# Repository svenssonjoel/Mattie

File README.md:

# Mattie
stM32f4 lATTIcE - MATTIE - A PCB with an STM32f4 and a LATTICE FPGA

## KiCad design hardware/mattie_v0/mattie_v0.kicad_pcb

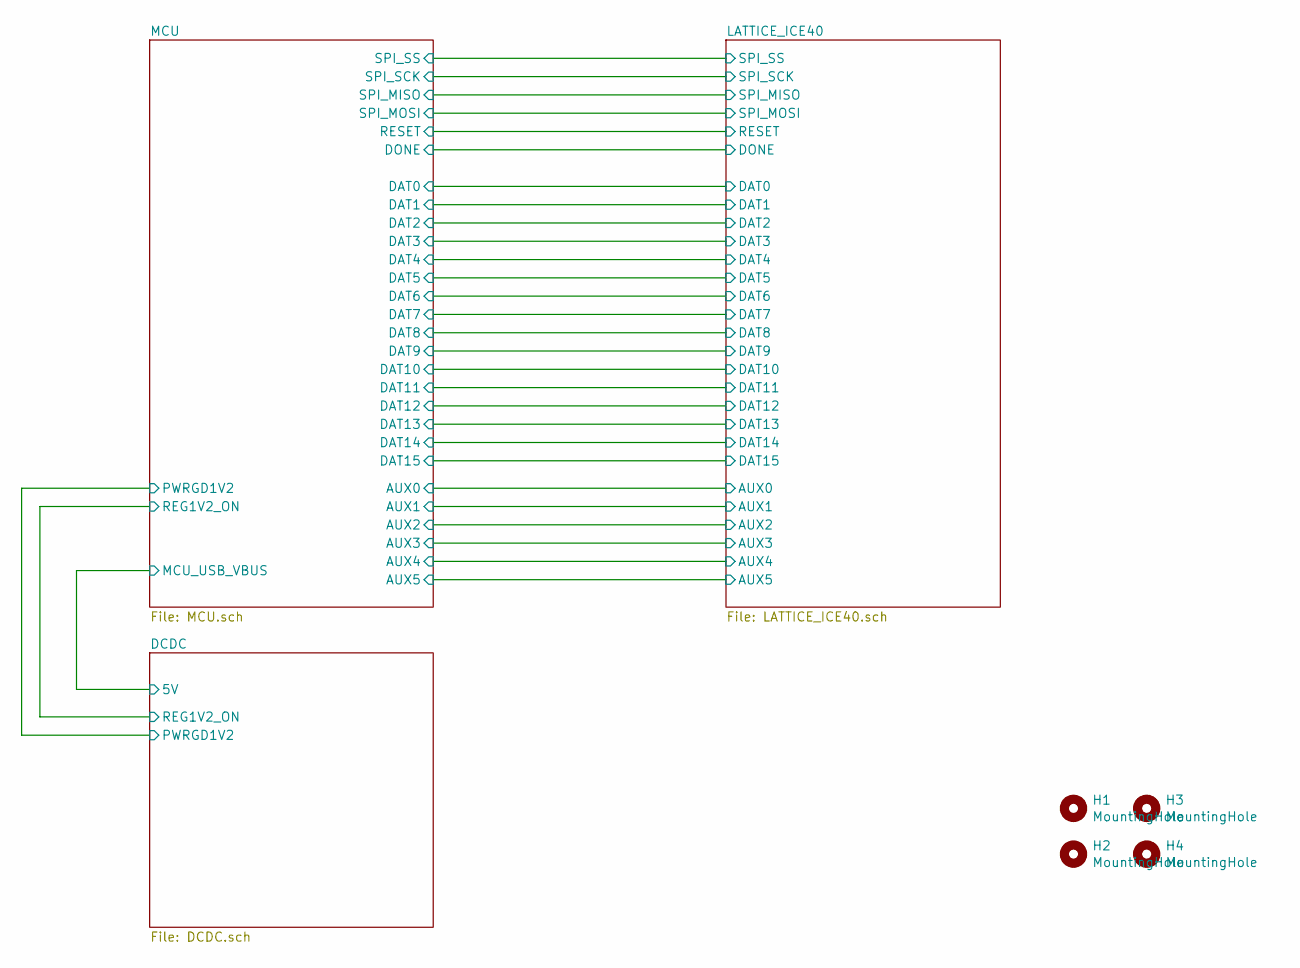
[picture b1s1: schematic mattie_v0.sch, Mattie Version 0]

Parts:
H1, H2, H3, H4: MountingHole; MountingHole_3.2mm_M3

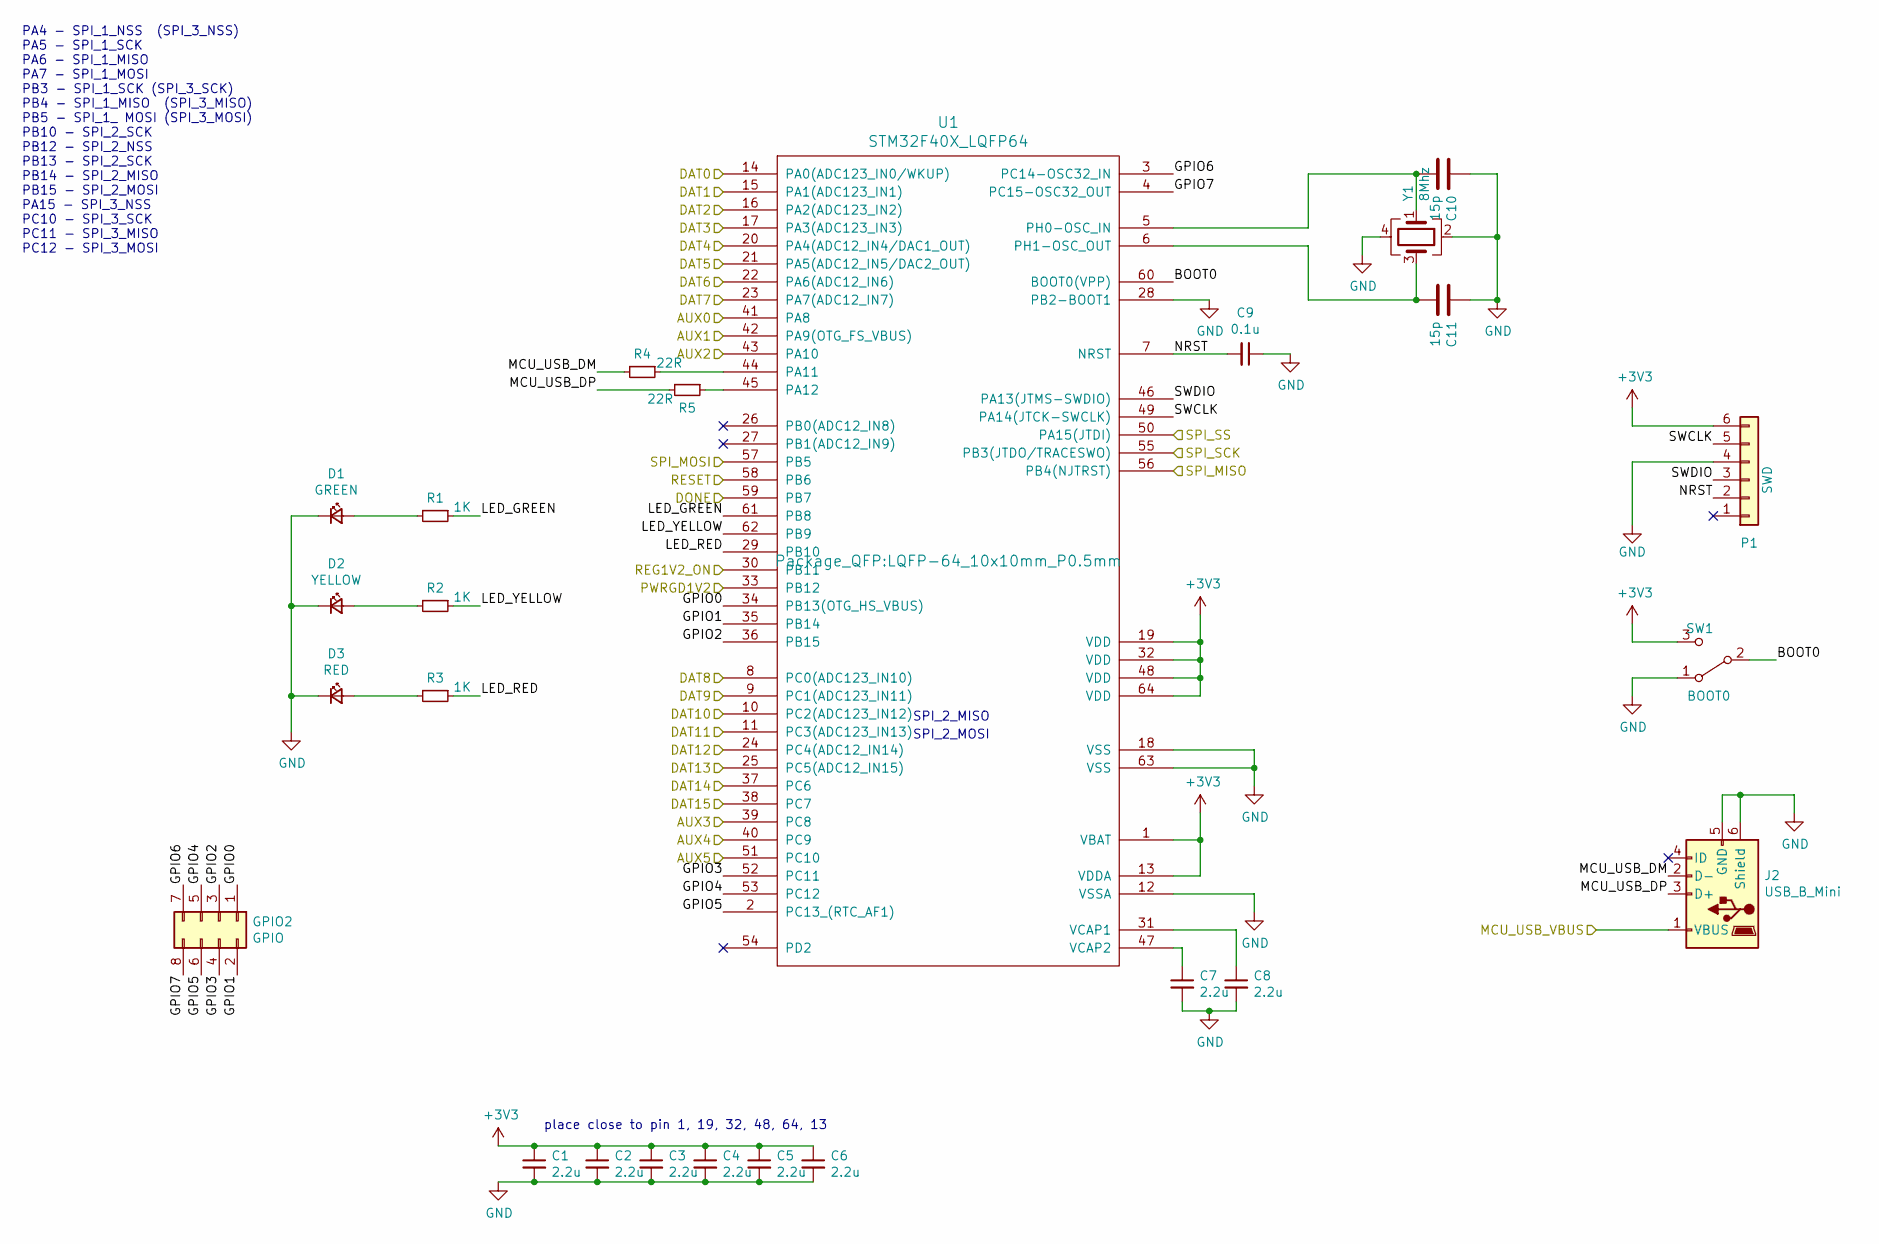
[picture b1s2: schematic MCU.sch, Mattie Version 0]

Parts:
C1, C2, C3, C4, C5, C6, C7, C8: 2.2u; C_0603_1608Metric
C9: 0.1u; C_0603_1608Metric
C10, C11: 15p; C_0603_1608Metric
D1: GREEN; LED_0603_1608Metric
D2: YELLOW; LED_0603_1608Metric
D3: RED; LED_0603_1608Metric
GPIO2: GPIO; PinHeader_2x04_P2.54mm_Vertical
J2: USB_B_Mini; USB_Mini-B_Lumberg_2486_01_Horizontal
P1: SWD; JST_PH_B6B-PH-K_1x06_P2.00mm_Vertical
R1, R2, R3: 1K; R_0603_1608Metric
R4, R5: 22R; R_0603_1608Metric
SW1: BOOT0; SW_SPDT_PCM12
U1: STM32F40X_LQFP64; LQFP-64_10x10mm_P0.5mm
Y1: 8Mhz; Crystal_SMD_5032-4Pin_5.0x3.2mm

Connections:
+3V3: C1.1, C2.1, C3.1, C4.1, C5.1, C6.1, P1.6, SW1.3 (C), U1.1 (VBAT), U1.13 (VDDA), U1.19 (VDD), U1.32 (VDD), U1.48 (VDD), U1.64 (VDD); also elsewhere on the board
/DCDC/5V: J2.1 (VBUS); also elsewhere on the board
/DCDC/PWRGD1V2: U1.33 (PB12); also elsewhere on the board
/DCDC/REG1V2_ON: U1.30 (PB11); also elsewhere on the board
/LATTICE_ICE40/AUX0: U1.41 (PA8); also elsewhere on the board
/LATTICE_ICE40/AUX1: U1.42 (PA9(OTG_FS_VBUS)); also elsewhere on the board
/LATTICE_ICE40/AUX2: U1.43 (PA10); also elsewhere on the board
/LATTICE_ICE40/AUX3: U1.39 (PC8); also elsewhere on the board
/LATTICE_ICE40/AUX4: U1.40 (PC9); also elsewhere on the board
/LATTICE_ICE40/AUX5: U1.51 (PC10); also elsewhere on the board
/LATTICE_ICE40/DAT0: U1.14 (PA0(ADC123_IN0/WKUP)); also elsewhere on the board
/LATTICE_ICE40/DAT1: U1.15 (PA1(ADC123_IN1)); also elsewhere on the board
/LATTICE_ICE40/DAT2: U1.16 (PA2(ADC123_IN2)); also elsewhere on the board
/LATTICE_ICE40/DAT3: U1.17 (PA3(ADC123_IN3)); also elsewhere on the board
/LATTICE_ICE40/DAT4: U1.20 (PA4(ADC12_IN4/DAC1_OUT)); also elsewhere on the board
/LATTICE_ICE40/DAT5: U1.21 (PA5(ADC12_IN5/DAC2_OUT)); also elsewhere on the board
/LATTICE_ICE40/DAT6: U1.22 (PA6(ADC12_IN6)); also elsewhere on the board
/LATTICE_ICE40/DAT7: U1.23 (PA7(ADC12_IN7)); also elsewhere on the board
/LATTICE_ICE40/DAT8: U1.8 (PC0(ADC123_IN10)); also elsewhere on the board
/LATTICE_ICE40/DAT9: U1.9 (PC1(ADC123_IN11)); also elsewhere on the board
/LATTICE_ICE40/DAT10: U1.10 (PC2(ADC123_IN12)); also elsewhere on the board
/LATTICE_ICE40/DAT11: U1.11 (PC3(ADC123_IN13)); also elsewhere on the board
/LATTICE_ICE40/DAT12: U1.24 (PC4(ADC12_IN14)); also elsewhere on the board
/LATTICE_ICE40/DAT13: U1.25 (PC5(ADC12_IN15)); also elsewhere on the board
/LATTICE_ICE40/DAT14: U1.37 (PC6); also elsewhere on the board
/LATTICE_ICE40/DAT15: U1.38 (PC7); also elsewhere on the board
/LATTICE_ICE40/DONE: U1.59 (PB7); also elsewhere on the board
/LATTICE_ICE40/RESET: U1.58 (PB6); also elsewhere on the board
/LATTICE_ICE40/SPI_MISO: U1.56 (PB4(NJTRST)); also elsewhere on the board
/LATTICE_ICE40/SPI_MOSI: U1.57 (PB5); also elsewhere on the board
/LATTICE_ICE40/SPI_SCK: U1.55 (PB3(JTDO/TRACESWO)); also elsewhere on the board
/LATTICE_ICE40/SPI_SS: U1.50 (PA15(JTDI)); also elsewhere on the board
/MCU/BOOT0: SW1.2 (B), U1.60 (BOOT0(VPP))
/MCU/GPIO0: GPIO2.1, U1.34 (PB13(OTG_HS_VBUS))
/MCU/GPIO1: GPIO2.2, U1.35 (PB14)
/MCU/GPIO2: GPIO2.3, U1.36 (PB15)
/MCU/GPIO3: GPIO2.4, U1.52 (PC11)
/MCU/GPIO4: GPIO2.5, U1.53 (PC12)
/MCU/GPIO5: GPIO2.6, U1.2 (PC13_(RTC_AF1))
/MCU/GPIO6: GPIO2.7, U1.3 (PC14-OSC32_IN)
/MCU/GPIO7: GPIO2.8, U1.4 (PC15-OSC32_OUT)
/MCU/LED_GREEN: R1.1, U1.61 (PB8)
/MCU/LED_RED: R3.1, U1.29 (PB10)
/MCU/LED_YELLOW: R2.1, U1.62 (PB9)
/MCU/MCU_USB_DM: J2.2 (D-), R4.2
/MCU/MCU_USB_DP: J2.3 (D+), R5.2
/MCU/NRST: C9.2, P1.2, U1.7 (NRST)
/MCU/SWCLK: P1.5, U1.49 (PA14(JTCK-SWCLK))
/MCU/SWDIO: P1.3, U1.46 (PA13(JTMS-SWDIO))
GND: C1.2, C2.2, C3.2, C4.2, C5.2, C6.2, C7.2, C8.2, C9.1, C10.1, C11.1, D1.1 (K), D2.1 (K), D3.1 (K), J2.5 (GND), J2.6 (Shield), P1.4, SW1.1 (A), U1.12 (VSSA), U1.18 (VSS), U1.28 (PB2-BOOT1), U1.63 (VSS), Y1.2, Y1.4; also elsewhere on the board
unnamed: C7.1, U1.47 (VCAP2)
unnamed: C8.1, U1.31 (VCAP1)
unnamed: C10.2, U1.5 (PH0-OSC_IN), Y1.1
unnamed: C11.2, U1.6 (PH1-OSC_OUT), Y1.3
unnamed: D1.2 (A), R1.2
unnamed: D2.2 (A), R2.2
unnamed: D3.2 (A), R3.2
unnamed: R4.1, U1.44 (PA11)
unnamed: R5.1, U1.45 (PA12)

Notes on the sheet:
SPI_2_MISO
SPI_2_MOSI
PA4 - SPI_1_NSS (SPI_3_NSS) PA5 - SPI_1_SCK PA6 - SPI_1_MISO PA7 - SPI_1_MOSI PB3 - SPI_1_SCK (SPI_3_SCK) PB4 - SPI_1_MISO (SPI_3_MISO) PB5 - SPI_1_ MOSI (SPI_3_MOSI) PB10 - SPI_2_SCK PB12 - SPI_2_NSS PB13 - SPI_2_SCK PB14 - SPI_2_MISO PB15 - SPI_2_MOSI PA15 - SPI_3_NSS PC10 - SPI_3_SCK PC11 - SPI_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
place close to pin 1, 19, 32, 48, 64, 13

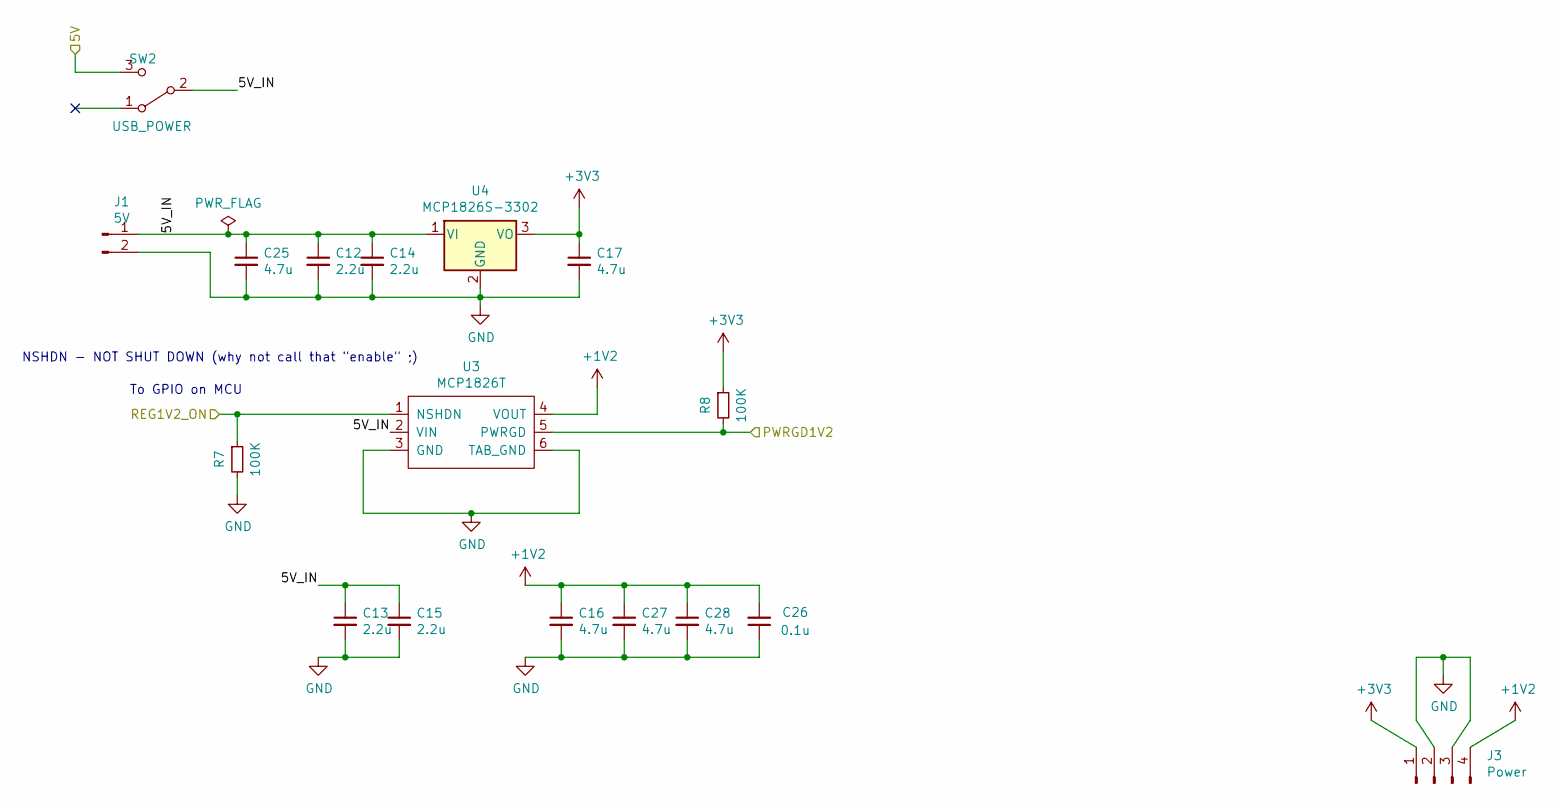
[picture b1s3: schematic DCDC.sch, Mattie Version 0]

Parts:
C12, C13, C14, C15: 2.2u; C_0603_1608Metric
C16, C17, C25, C27, C28: 4.7u; C_0603_1608Metric
C26: 0.1u; C_0603_1608Metric
J1: 5V; PinHeader_1x02_P2.54mm_Vertical
J3: Power; PinHeader_1x04_P2.54mm_Vertical
R7, R8: 100K; R_0603_1608Metric
SW2: USB_POWER; SW_SPDT_PCM12
U3: MCP1826T; SOT-223-6
U4: MCP1826S-3302; SOT-223-3_TabPin2

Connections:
+1V2: C16.1, C26.2, C27.1, C28.1, J3.4, U3.4 (VOUT); also elsewhere on the board
+3V3: C17.1, J3.1, R8.1, U4.3 (VO); also elsewhere on the board
/DCDC/5V: SW2.3 (C); also elsewhere on the board
/DCDC/5V_IN: C12.1, C13.1, C14.1, C15.1, C25.1, J1.1, SW2.2 (B), U3.2 (VIN), U4.1 (VI)
/DCDC/PWRGD1V2: R8.2, U3.5 (PWRGD); also elsewhere on the board
/DCDC/REG1V2_ON: R7.1, U3.1 (NSHDN); also elsewhere on the board
GND: C12.2, C13.2, C14.2, C15.2, C16.2, C17.2, C25.2, C26.1, C27.2, C28.2, J1.2, J3.2, J3.3, R7.2, U3.3 (GND), U3.6 (TAB_GND), U4.2 (GND); also elsewhere on the board

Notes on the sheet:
To GPIO on MCU
NSHDN - NOT SHUT DOWN (why not call that "enable" ;)

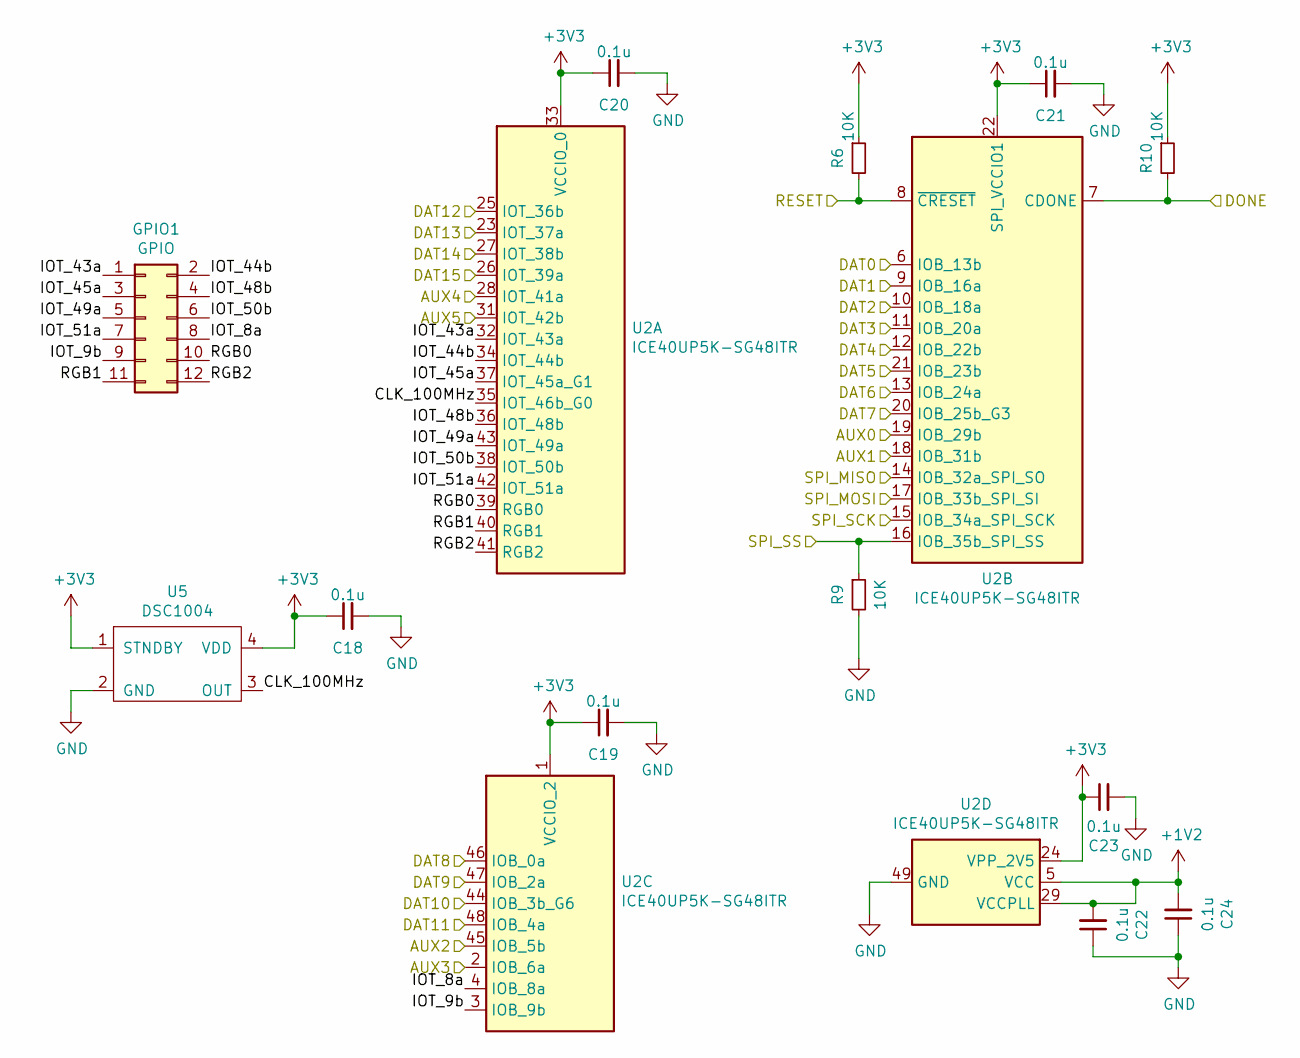
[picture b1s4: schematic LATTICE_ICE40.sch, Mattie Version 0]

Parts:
C18, C19, C20, C21, C22, C23, C24: 0.1u; C_0603_1608Metric
GPIO1: GPIO; PinHeader_2x06_P2.54mm_Vertical
R6, R9, R10: 10K; R_0603_1608Metric
U2: ICE40UP5K-SG48ITR; QFN-48-1EP_7x7mm_P0.5mm_EP5.45x5.45mm_ThermalVias
U5: DSC1004

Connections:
+1V2: C22.2, C24.2, U2.5 (VCC), U2.29 (VCCPLL), U2.30 (VCC); also elsewhere on the board
+3V3: C18.1, C19.1, C20.1, C21.1, C23.1, R6.1, R10.1, U2.1 (VCCIO_2), U2.22 (SPI_VCCIO1), U2.24 (VPP_2V5), U2.33 (VCCIO_0), U5.1 (STNDBY), U5.4 (VDD); also elsewhere on the board
/LATTICE_ICE40/AUX0: U2.19 (IOB_29b); also elsewhere on the board
/LATTICE_ICE40/AUX1: U2.18 (IOB_31b); also elsewhere on the board
/LATTICE_ICE40/AUX2: U2.45 (IOB_5b); also elsewhere on the board
/LATTICE_ICE40/AUX3: U2.2 (IOB_6a); also elsewhere on the board
/LATTICE_ICE40/AUX4: U2.28 (IOT_41a); also elsewhere on the board
/LATTICE_ICE40/AUX5: U2.31 (IOT_42b); also elsewhere on the board
/LATTICE_ICE40/CLK_100MHz: U2.35 (IOT_46b_G0), U5.3 (OUT)
/LATTICE_ICE40/DAT0: U2.6 (IOB_13b); also elsewhere on the board
/LATTICE_ICE40/DAT1: U2.9 (IOB_16a); also elsewhere on the board
/LATTICE_ICE40/DAT2: U2.10 (IOB_18a); also elsewhere on the board
/LATTICE_ICE40/DAT3: U2.11 (IOB_20a); also elsewhere on the board
/LATTICE_ICE40/DAT4: U2.12 (IOB_22b); also elsewhere on the board
/LATTICE_ICE40/DAT5: U2.21 (IOB_23b); also elsewhere on the board
/LATTICE_ICE40/DAT6: U2.13 (IOB_24a); also elsewhere on the board
/LATTICE_ICE40/DAT7: U2.20 (IOB_25b_G3); also elsewhere on the board
/LATTICE_ICE40/DAT8: U2.46 (IOB_0a); also elsewhere on the board
/LATTICE_ICE40/DAT9: U2.47 (IOB_2a); also elsewhere on the board
/LATTICE_ICE40/DAT10: U2.44 (IOB_3b_G6); also elsewhere on the board
/LATTICE_ICE40/DAT11: U2.48 (IOB_4a); also elsewhere on the board
/LATTICE_ICE40/DAT12: U2.25 (IOT_36b); also elsewhere on the board
/LATTICE_ICE40/DAT13: U2.23 (IOT_37a); also elsewhere on the board
/LATTICE_ICE40/DAT14: U2.27 (IOT_38b); also elsewhere on the board
/LATTICE_ICE40/DAT15: U2.26 (IOT_39a); also elsewhere on the board
/LATTICE_ICE40/DONE: R10.2, U2.7 (CDONE); also elsewhere on the board
/LATTICE_ICE40/IOT_8a: GPIO1.8, U2.4 (IOB_8a)
/LATTICE_ICE40/IOT_9b: GPIO1.9, U2.3 (IOB_9b)
/LATTICE_ICE40/IOT_43a: GPIO1.1, U2.32 (IOT_43a)
/LATTICE_ICE40/IOT_44b: GPIO1.2, U2.34 (IOT_44b)
/LATTICE_ICE40/IOT_45a: GPIO1.3, U2.37 (IOT_45a_G1)
/LATTICE_ICE40/IOT_48b: GPIO1.4, U2.36 (IOT_48b)
/LATTICE_ICE40/IOT_49a: GPIO1.5, U2.43 (IOT_49a)
/LATTICE_ICE40/IOT_50b: GPIO1.6, U2.38 (IOT_50b)
/LATTICE_ICE40/IOT_51a: GPIO1.7, U2.42 (IOT_51a)
/LATTICE_ICE40/RESET: R6.2, U2.8 (~CRESET); also elsewhere on the board
/LATTICE_ICE40/RGB0: GPIO1.10, U2.39 (RGB0)
/LATTICE_ICE40/RGB1: GPIO1.11, U2.40 (RGB1)
/LATTICE_ICE40/RGB2: GPIO1.12, U2.41 (RGB2)
/LATTICE_ICE40/SPI_MISO: U2.14 (IOB_32a_SPI_SO); also elsewhere on the board
/LATTICE_ICE40/SPI_MOSI: U2.17 (IOB_33b_SPI_SI); also elsewhere on the board
/LATTICE_ICE40/SPI_SCK: U2.15 (IOB_34a_SPI_SCK); also elsewhere on the board
/LATTICE_ICE40/SPI_SS: R9.1, U2.16 (IOB_35b_SPI_SS); also elsewhere on the board
GND: C18.2, C19.2, C20.2, C21.2, C22.1, C23.2, C24.1, R9.2, U2.49 (GND), U5.2 (GND); also elsewhere on the board

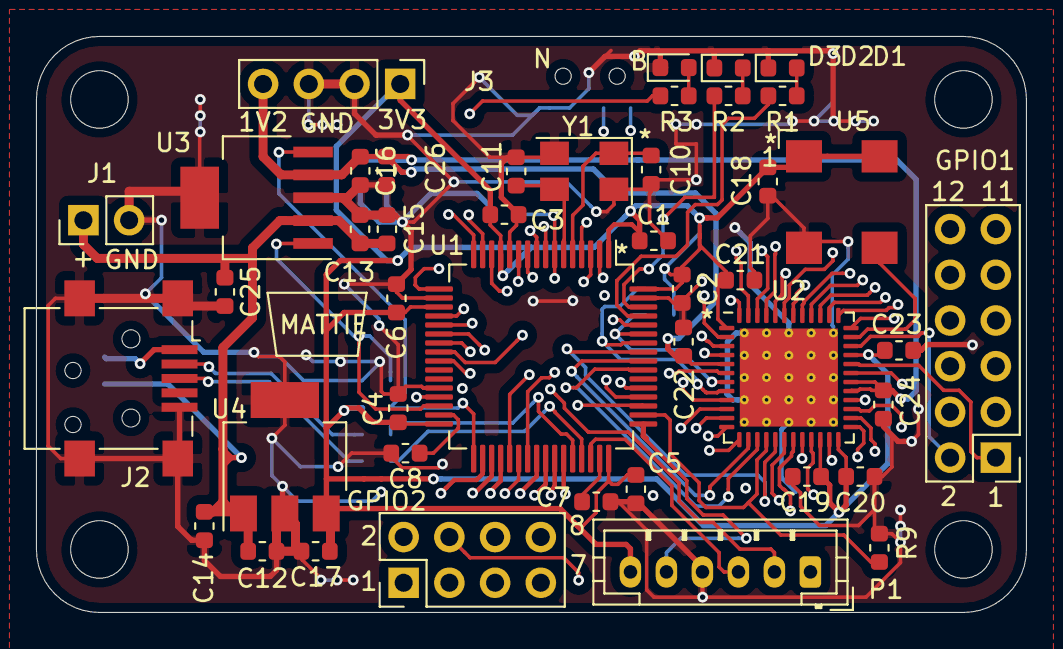
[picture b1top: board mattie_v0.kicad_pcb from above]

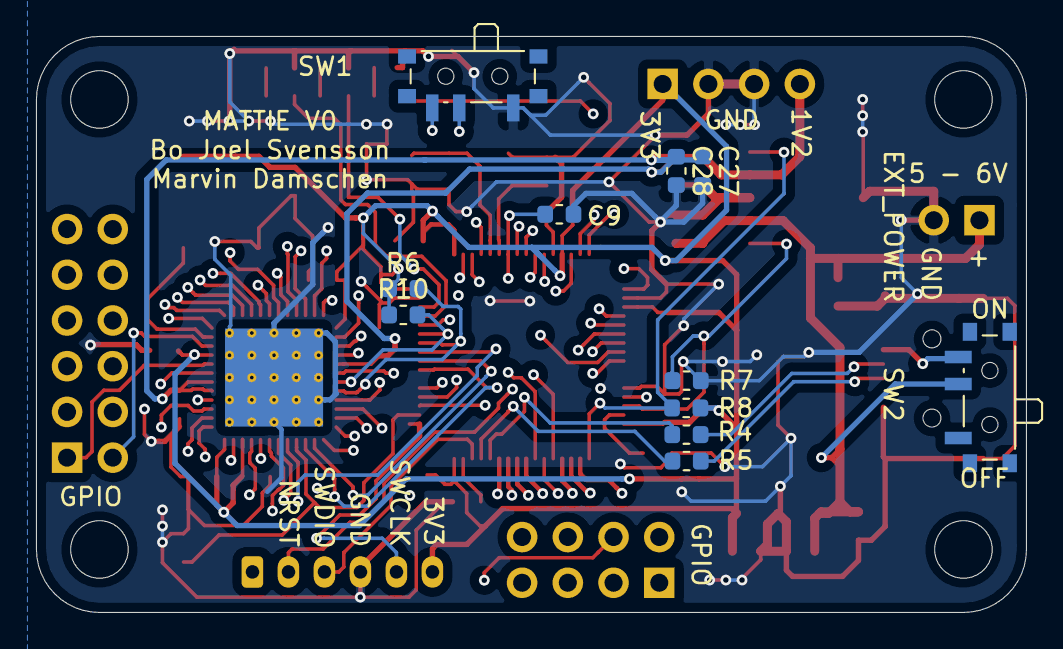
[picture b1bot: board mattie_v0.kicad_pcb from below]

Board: 4 copper layers, 55.0 x 32.0 mm, 59 parts (11 on the bottom side), 74 nets.

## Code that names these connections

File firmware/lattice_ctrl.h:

/*
    Copyright 2020 Joel Svensson	svenssonjoel@yahoo.se

    This program is free software: you can redistribute it and/or modify
    it under the terms of the GNU General Public License as published by
    the Free Software Foundation, either version 3 of the License, or
    (at your option) any later version.

    This program is distributed in the hope that it will be useful,
    but WITHOUT ANY WARRANTY; without even the implied warranty of
    MERCHANTABILITY or FITNESS FOR A PARTICULAR PURPOSE.  See the
    GNU General Public License for more details.

    You should have received a copy of the GNU General Public License
    along with this program.  If not, see <http://www.gnu.org/licenses/>.
*/

#ifndef _LATTICE_CTRL_H_
#define _LATTICE_CTRL_H_

#include "hal.h"
#include "ch.h"

#define RESET_GPIO GPIOB
#define RESET_PIN  6

#define DONE_GPIO GPIOB
#define DONE_PIN  7

#define SPI_SS_GPIO   GPIOA 
#define SPI_SS_PIN    15
#define SPI_SCK_GPIO  GPIOB 
#define SPI_SCK_PIN   3 
#define SPI_MISO_GPIO GPIOB
#define SPI_MISO_PIN  4 
#define SPI_MOSI_GPIO GPIOB
#define SPI_MOSI_PIN  5


/* Initialize the controll interface to the FPGA (SPI + RESET + DONE) */ 
void lattice_ctrl_init(void); 

/* RESET the FPGA */
bool lattice_ctrl_reset(void);

#endif

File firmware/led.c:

#include "led.h"

#include "hal.h"
#include "hal_pal.h"

void led_write(int num, int state) {
  switch (num) {
  case LED_RED:
    palWritePad(GPIOB, LED_RED_PIN, state);
    break;

  case LED_GREEN:
    palWritePad(GPIOB, LED_GREEN_PIN, state);
    break;

  case LED_YELLOW:
    palWritePad(GPIOB, LED_YELLOW_PIN, state);
    break;

  default:
    break;
  }
}

void led_init(void) {
  palSetPadMode(GPIOB, LED_RED_PIN,
		PAL_MODE_OUTPUT_PUSHPULL |
		PAL_STM32_OSPEED_HIGHEST);
  palSetPadMode(GPIOB, LED_GREEN_PIN,
		PAL_MODE_OUTPUT_PUSHPULL |
		PAL_STM32_OSPEED_HIGHEST);
  palSetPadMode(GPIOB, LED_YELLOW_PIN,
		PAL_MODE_OUTPUT_PUSHPULL |
		PAL_STM32_OSPEED_HIGHEST);

  led_write(LED_RED, 0);
  led_write(LED_GREEN, 0);
  led_write(LED_YELLOW, 0);
}

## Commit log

2020-04-09 added some datasheets etc
2020-04-09 added some component ideas to components. Should look at their datasheets in more detail
2020-04-09 added 1.2V LDO datasheet
2020-04-09 added 3.3V LDO datasheet
2020-04-09 more component options
2020-04-09 added a dc power connected if we need it
2020-04-09 added the hardware checklist for ICE40
2020-04-09 added another LDO for 2.5V
2020-04-09 added some more iCE40 info
2020-04-09 added some alternative LDOs with less pins
2020-04-15 added 100MHz Oscillator
2020-04-15 adding 8MHz clock for the MCU
2020-04-16 started sketching
2020-04-18 dcdc
2020-04-18 some tweaks
2020-04-21 routing
2020-04-21 tweaking and cleaning
2020-04-21 tweaks
2020-04-22 added powerswitch for USB power
2020-04-23 minitweak
2020-04-23 adding some cap
2020-04-23 added pullups and pulldowns
2020-04-23 Changed some cap values and added extra caps
2020-05-07 starting on firmware
2020-05-07 added schematics for reference
2020-05-07 rename of binary
2020-05-07 added some initialization code
2020-05-07 added some flashing LEDs
2020-05-07 experimenting with SPI... no idea so far
2020-05-07 turning powersupply for FPGA on and checking for pwrgd then performs a reset and checks for success
2020-05-07 added function that configures direction on 4 different groups of IOs connected to the FPGA
2020-05-07 setting all MCU <-> FPGA connections to inputs (at MCU end)
2020-05-08 flash yellow led if reset of FPGA is ok
2020-05-09 restored kicad_pcb from old commit
2020-05-11 trying to understand the SPI configuration
